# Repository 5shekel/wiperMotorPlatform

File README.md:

# wiperMotorPlatform
based on 2 wiper motors, NRF24 and a VNH2SP30 motor driver based arduino shield

##relay guides
http://www.learningaboutelectronics.com/Articles/DPDT-relay-wiring-diagram

http://www.me.umn.edu/courses/me2011/arduino/technotes/dcmotors/bidirectional/bidirMotor.html

[relay DPDT online simulation](http://lushprojects.com/circuitjs/circuitjs.html?cct=$+1+0.000005+10.200277308269968+50+5+50%0A178+256+208+400+208+0+2+0.2+0.2585230348539524+0.05+1000000+0.02+20%0A172+224+208+160+208+0+6+12+12+0+0+0.5+Coil+Voltage%0Ag+256+320+256+352+0%0A181+544+160+592+160+0+300.0680411695022+100+120+0.4+0.4%0A181+544+224+592+224+0+300.0064191237612+100+120+0.4+0.4%0Aw+544+160+544+224+0%0Ad+592+160+640+160+1+0.805904783%0Ad+640+224+592+224+1+0.805904783%0Aw+640+160+640+224+0%0Aw+400+144+432+144+0%0Aw+432+144+432+224+0%0Aw+432+224+400+224+0%0Aw+400+176+400+192+0%0Aw+256+240+224+240+0%0Aw+256+208+224+208+0%0Aw+400+176+512+176+0%0Aw+512+224+432+224+0%0Aw+512+160+544+160+0%0Aw+512+224+512+256+0%0Aw+512+256+640+256+0%0Aw+640+224+640+256+0%0Ax+551+245+627+248+0+18+DC+motor%0Aw+512+160+512+176+0%0At+224+304+256+304+0+1+-6.114769651509018+0.7147696515114635+100%0Aw+256+256+256+288+0%0Aw+224+240+224+208+0%0AR+64+304+16+304+0+0+40+3.3+0+0+0.5%0Ar+176+304+208+304+0+1000%0Af+176+112+224+112+0+1.5%0Ag+224+128+224+160+0%0Ar+176+112+144+112+0+1000%0As+64+112+144+112+0+1+false%0Aw+224+96+224+64+0%0Aw+256+96+256+160+0%0Aw+64+304+64+112+0%0As+64+304+144+304+0+0+false%0Aw+176+304+144+304+0%0Aw+224+304+208+304+0%0Ax+53+85+187+88+0+24+on/off+(pwm)%0Ax+60+333+151+336+0+24+direction%0Aw+224+64+256+64+0%0Aw+256+64+256+96+0%0Ad+256+160+256+208+1+0.805904783%0A)

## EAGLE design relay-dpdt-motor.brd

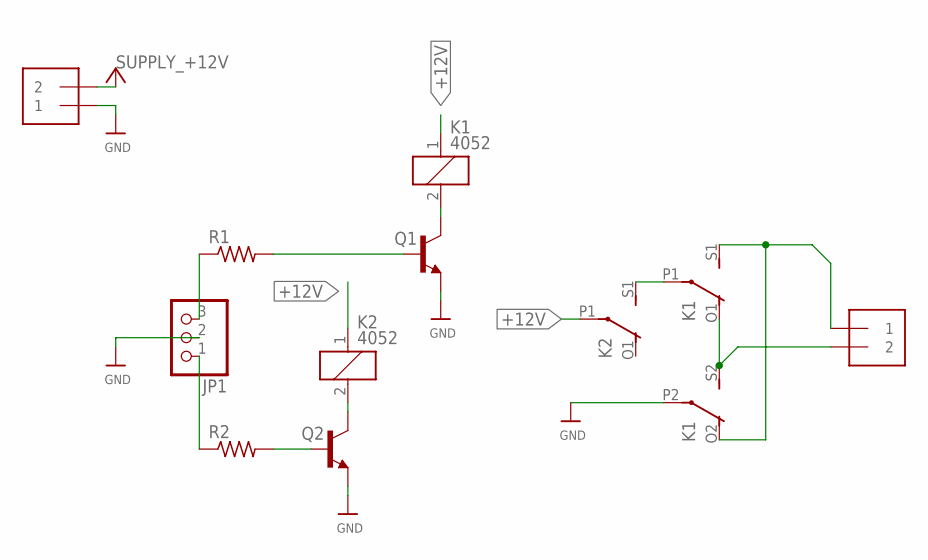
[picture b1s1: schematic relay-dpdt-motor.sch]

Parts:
J1, J2: 1X2-3.5MM
JP1: PINHD-1X3CB; 1X03-CLEANBIG
K1, K2: 4052; F4052
Q1, Q2: TRANSISTOR_BJT_NPN-TO-92-EBC; TO-92
R1, R2: R-US_0204/7; 0204/7

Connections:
+12V: J1.2, K1.1, K2.1, K2.P1
GND: J1.1, JP1.2, K1.P2, Q1.1 (E), Q2.1 (E)
unnamed: Q1.2 (B), R1.2
unnamed: K1.P1, K2.S1 (S)
unnamed: Q2.2 (B), R2.2
unnamed: K2.2, Q2.3 (C)
unnamed: JP1.1, R2.1
unnamed: J2.1, K1.O2 (O), K1.S1 (S)
unnamed: J2.2, K1.O1 (O), K1.S2 (S)
unnamed: K1.2, Q1.3 (C)
unnamed: JP1.3, R1.1

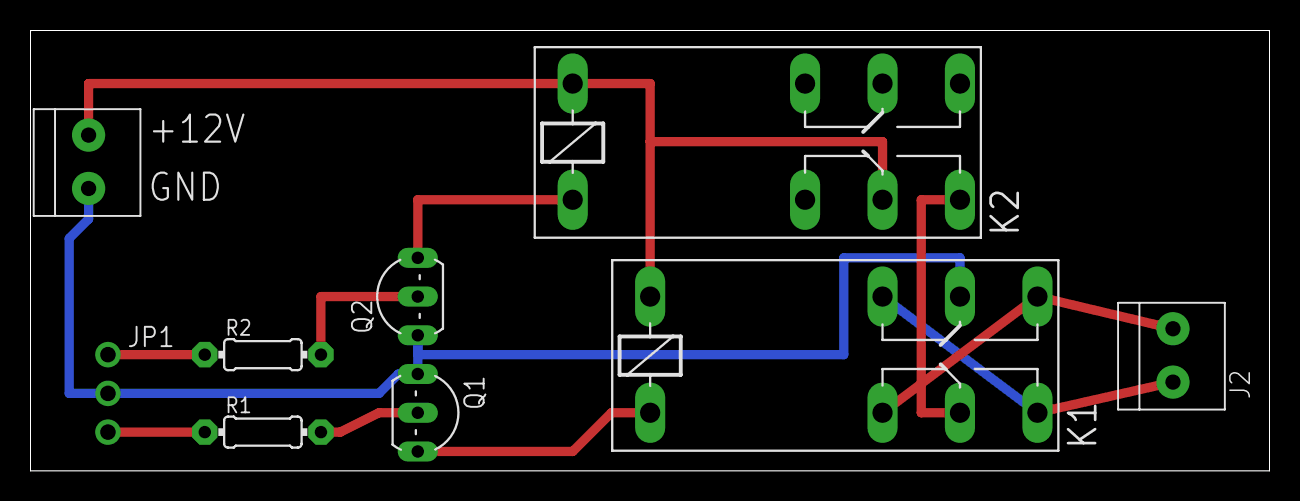
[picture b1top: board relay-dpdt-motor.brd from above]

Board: 2 copper layers, 81.3 x 28.9 mm, 9 parts (0 on the bottom side), 11 nets.

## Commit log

2015-06-17 working version with nano vs mini. with proper data struct '
2015-06-18 its working, but the motion is messy. probebly beacuse the oriontation of the joystick is wrong or somehting
2015-11-06 add pic
2015-11-06 ad pics
2016-02-21 misc changes
2016-04-12 relay version based on http://www.me.umn.edu/courses/me2011/arduino/technotes/dcmotors/bidirectional/bidirMotor.html
2016-04-12 falstad.com circuit simualtor
2016-04-12 working sim, no mcu
2016-04-12 working sim, with MCU and flyback diode
2016-04-12 removed new work
2016-04-12 readme
2016-04-12 eagle prewired
2016-04-12 brd update, wired
2016-04-12 sim update, PNP
2016-04-12 with pnp
2016-04-12 2 relays one cup, including flyback
2016-04-12 2 relays one cup, new sim
2016-04-13 working relay, but i returned to using the monstermotor shield. and now with beter stop code for the motors

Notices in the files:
parts and their libraries:
microbuilder: This work is placed in the public domain, and may be freely used for commercial and non-commercial work with the following conditions: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
